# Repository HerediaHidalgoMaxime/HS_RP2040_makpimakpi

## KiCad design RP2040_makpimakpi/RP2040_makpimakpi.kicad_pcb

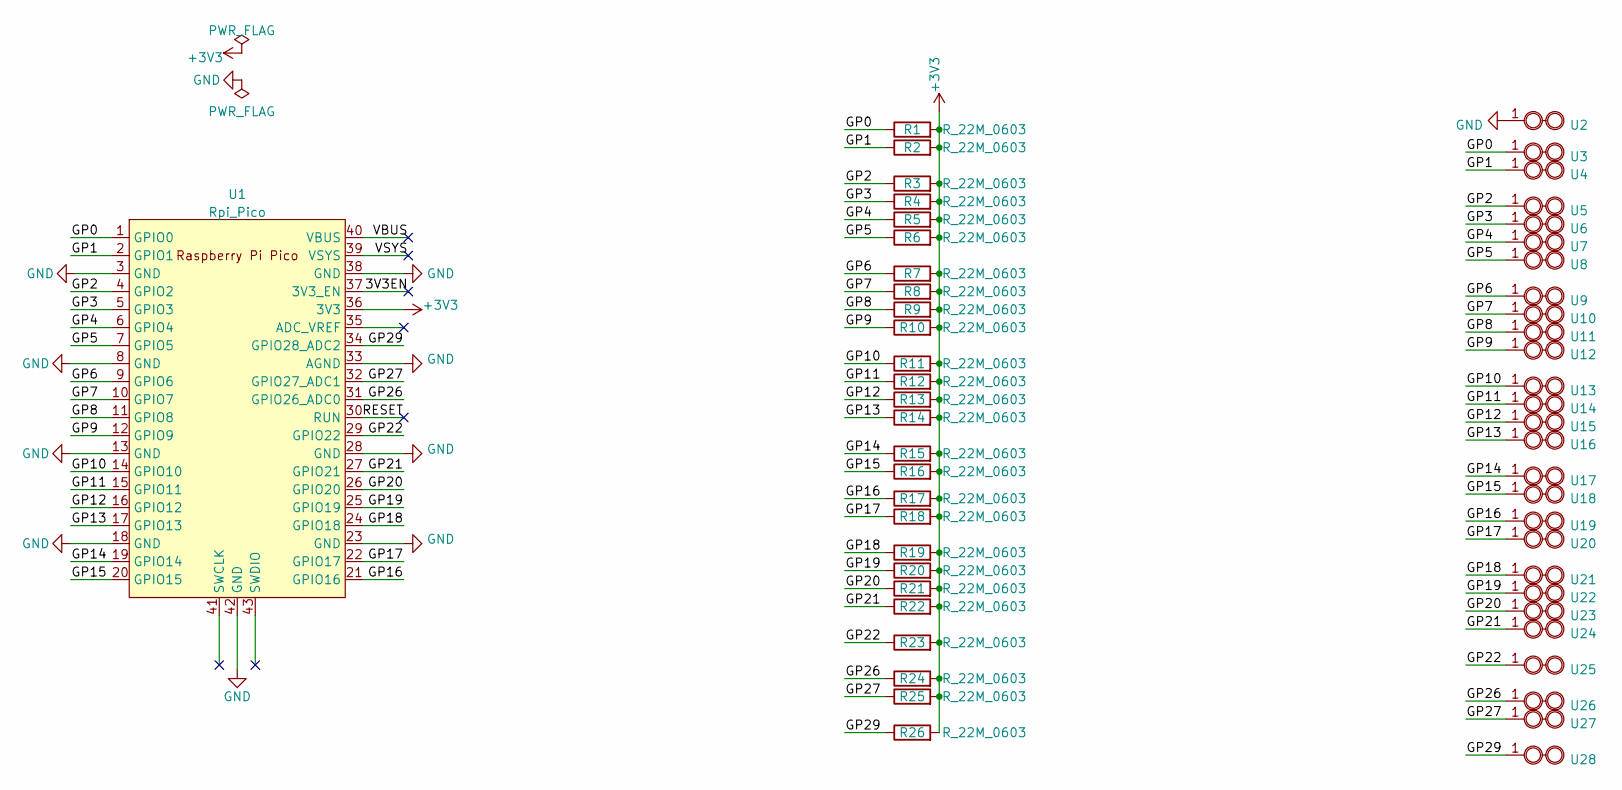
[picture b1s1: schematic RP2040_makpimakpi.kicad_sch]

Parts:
R1, R2, R3, R4, R5, R6, R7, R8, R9, R10, R11, R12, R13, R14, R15, R16, R17, R18, R19, R20, R21, R22, R23, R24, R25, R26: R_22M_0603; R_0603_1608Metric_Pad0.98x0.95mm_HandSolder
U1: Rpi_Pico; RPi_Pico_SMD_TH
U2, U3, U4, U5, U6, U7, U8, U9, U10, U11, U12, U13, U14, U15, U16, U17, U18, U19, U20, U21, U22, U23, U24, U25, U26, U27, U28: AlligatorClip

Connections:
+3V3: R1.2, R2.2, R3.2, R4.2, R5.2, R6.2, R7.2, R8.2, R9.2, R10.2, R11.2, R12.2, R13.2, R14.2, R15.2, R16.2, R17.2, R18.2, R19.2, R20.2, R21.2, R22.2, R23.2, R24.2, R25.2, R26.2, U1.36 (3V3)
/3V3EN: U1.37 (3V3_EN)
/GP0: R1.1, U1.1 (GPIO0), U3.1
/GP1: R2.1, U1.2 (GPIO1), U4.1
/GP2: R3.1, U1.4 (GPIO2), U5.1
/GP3: R4.1, U1.5 (GPIO3), U6.1
/GP4: R5.1, U1.6 (GPIO4), U7.1
/GP5: R6.1, U1.7 (GPIO5), U8.1
/GP6: R7.1, U1.9 (GPIO6), U9.1
/GP7: R8.1, U1.10 (GPIO7), U10.1
/GP8: R9.1, U1.11 (GPIO8), U11.1
/GP9: R10.1, U1.12 (GPIO9), U12.1
/GP10: R11.1, U1.14 (GPIO10), U13.1
/GP11: R12.1, U1.15 (GPIO11), U14.1
/GP12: R13.1, U1.16 (GPIO12), U15.1
/GP13: R14.1, U1.17 (GPIO13), U16.1
/GP14: R15.1, U1.19 (GPIO14), U17.1
/GP15: R16.1, U1.20 (GPIO15), U18.1
/GP16: R17.1, U1.21 (GPIO16), U19.1
/GP17: R18.1, U1.22 (GPIO17), U20.1
/GP18: R19.1, U1.24 (GPIO18), U21.1
/GP19: R20.1, U1.25 (GPIO19), U22.1
/GP20: R21.1, U1.26 (GPIO20), U23.1
/GP21: R22.1, U1.27 (GPIO21), U24.1
/GP22: R23.1, U1.29 (GPIO22), U25.1
/GP26: R24.1, U1.31 (GPIO26_ADC0), U26.1
/GP27: R25.1, U1.32 (GPIO27_ADC1), U27.1
/GP29: R26.1, U1.34 (GPIO28_ADC2), U28.1
/RESET: U1.30 (RUN)
/VBUS: U1.40 (VBUS)
/VSYS: U1.39 (VSYS)
GND: U1.3 (GND), U1.8 (GND), U1.13 (GND), U1.18 (GND), U1.23 (GND), U1.28 (GND), U1.33 (AGND), U1.38 (GND), U1.42 (GND), U2.1

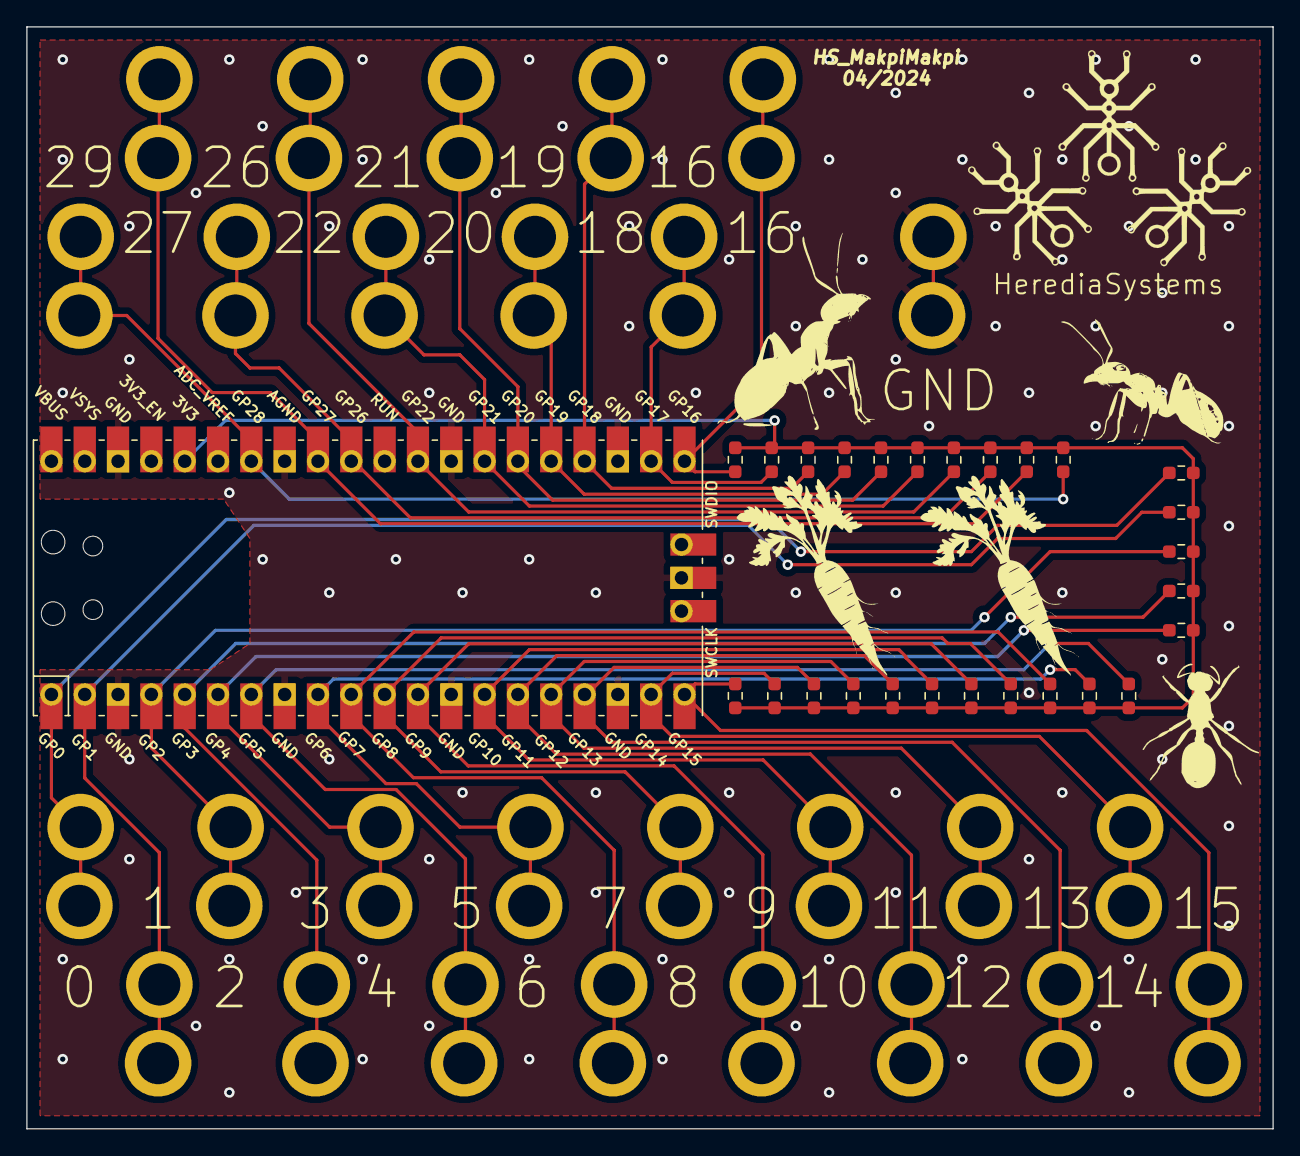
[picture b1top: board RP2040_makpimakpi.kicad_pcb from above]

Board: 2 copper layers, 95.0 x 84.0 mm, 54 parts (0 on the bottom side), 28 nets.

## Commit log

2024-06-02 Arduino example code
2024-06-02 PCB V0.1
